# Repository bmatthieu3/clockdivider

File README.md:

# Clock Divider module - Demo [here](https://youtu.be/5VTIWuq25X8)

A clock divider is usually a very important module in a modular synth as it can allow you to give the tempo to many other modules of your synth.
Here are some useful examples showing why it can be good to have a clock divider:

* Provide a /2, /4, /8 clock allowing to trigger drum sounds every 2, 4 or 8 cycles or any other events.
* Do Polyrhythm thanks to impair dividing ratio: /3, /5, /7!
* Mess a little bit the rythm thanks to a CV rotating input. This input accepts 0->5 volts. 0 volt means the outputs are not rotated, the first output gives a clock having the same frequency, the second one having half the input clock frequency, the third having one-third of the frequency... 5/8 volt will rotate the outputs of one output: the first output will be one-eight of the input clock frequency, the second output will give the same frequency, the third output will give the half of the input frequency... the eight's output will give one-seven of the first frequency.

# What does this repo contain

* The code for the Atmega328p in clock_divider.ino
* The electrical scheme for the module openable with kicad

* The pcd footprint for kicad (There is a 1k resistor missing between VCC (5V) and pin 6 of the uC. This is for the dividing potar to work, the main features (division of the clock signal frequency by 1 -> 8, the reset of the outputs and the rotating CV) will work without correcting this).
* The .svg showing the interface plate of the module. This is a very simple one that I did very fast, it is not very good at all. I recommand you to do your own if you want to build the module for your own synth. It will be of your taste and what is from you is always the best as a DIYer.
* The .stl file of the interface plate (made with blender)
* The .stl transformed in .gcode to print it.

# What does it look like

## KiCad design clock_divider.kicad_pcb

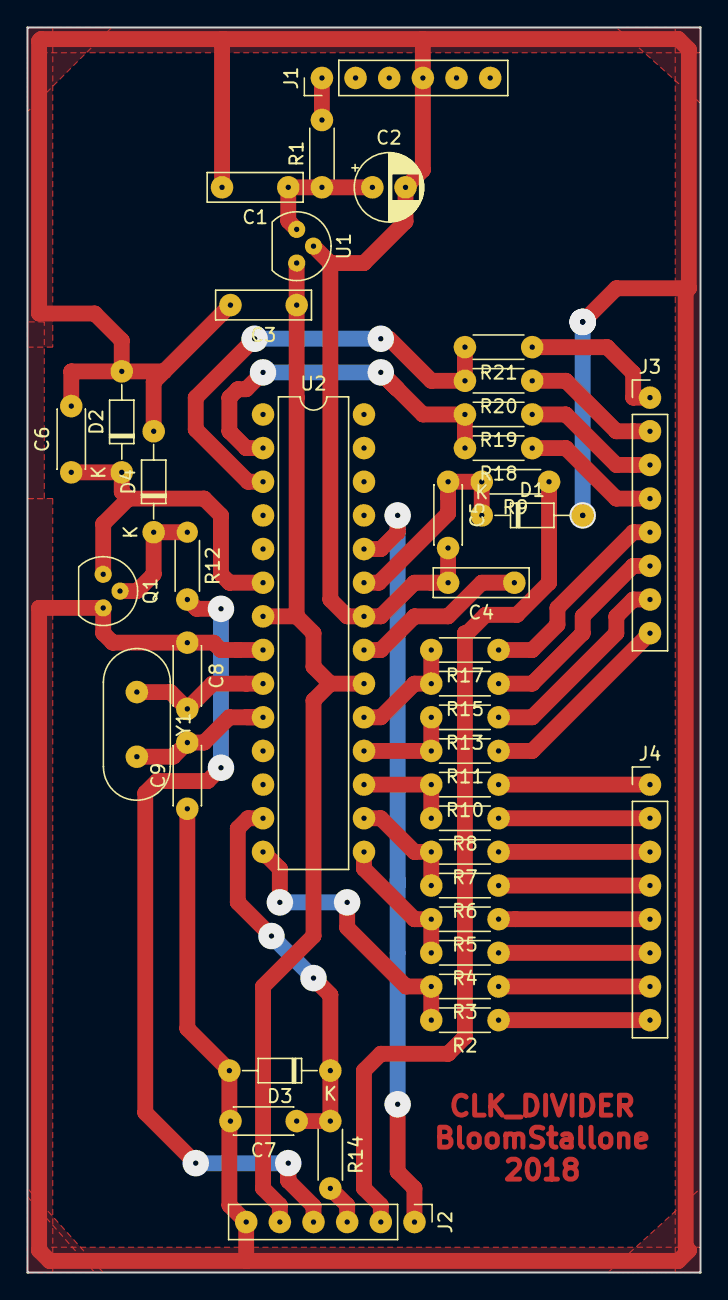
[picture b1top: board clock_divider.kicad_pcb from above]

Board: 2 copper layers, 50.8 x 94.0 mm, 41 parts (0 on the bottom side), 39 nets.

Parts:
C1, C3, C4: 100nF; C_Rect_L7.0mm_W2.0mm_P5.00mm
C2: 22uF; CP_Radial_D5.0mm_P2.50mm
C5, C6, C7: 220pF; C_Disc_D4.3mm_W1.9mm_P5.00mm
C8, C9: 22pF; C_Disc_D4.3mm_W1.9mm_P5.00mm
D1, D2, D3: D_Zener; D_DO-34_SOD68_P7.62mm_Horizontal
D4: D; D_DO-34_SOD68_P7.62mm_Horizontal
J1, J2: Conn_01x06_Male; PinHeader_1x06_P2.54mm_Vertical
J3, J4: Conn_01x08_Male; PinHeader_1x08_P2.54mm_Vertical
Q1: BC547; TO-92
R1: 10; R_Axial_DIN0204_L3.6mm_D1.6mm_P5.08mm_Horizontal
R2, R4, R6, R8, R11, R15, R18, R20: 330; R_Axial_DIN0204_L3.6mm_D1.6mm_P5.08mm_Horizontal
R3, R5, R7, R9, R10, R13, R14, R17, R19, R21: 1k; R_Axial_DIN0204_L3.6mm_D1.6mm_P5.08mm_Horizontal
R12: 470k; R_Axial_DIN0204_L3.6mm_D1.6mm_P5.08mm_Horizontal
U1: L7805; TO-92
U2: ATmega328-PU; DIP-28_W7.62mm
Y1: Crystal; Crystal_HC49-4H_Vertical

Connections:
/CLK1: J4.7, R3.1
/CLK2: J4.5, R5.1
/CLK3: J4.3, R7.1
/CLK4: J4.1, R10.1
/CLK5: J3.7, R13.1
/CLK6: J3.5, R17.1
/CLK7: J3.3, R19.1
/CLK8: J3.1, R21.1
/DIVIDING: J2.1, U2.24
/LED1: J4.8, R2.1
/LED2: J4.6, R4.1
/LED3: J4.4, R6.1
/LED4: J4.2, R8.1
/LED5: J3.8, R11.1
/LED6: J3.6, R15.1
/LED7: J3.4, R18.1
/LED8: J3.2, R20.1
/MASTER_CLK_IN: J2.3, R14.2
/PB0: R2.2, R3.2, U2.14
/PB1: R4.2, R5.2, U2.15
/PB2: R6.2, R7.2, U2.16
/PB3: R8.2, R10.2, U2.17
/PB4: R11.2, R13.2, U2.18
/PB5: R15.2, R17.2, U2.19
/PD0: R18.2, R19.2, U2.2
/PD1: R20.2, R21.2, U2.3
/RESET_IN: J2.4, R12.2
/ROTATE_IN: J2.2, R9.1
/VCC: C3.1, J2.5, U1.3, U2.7, U2.20
GND: C1.2, C2.2, C3.2, C4.2, C5.2, C6.2, C7.2, C8.1, C9.1, D1.2, D2.2, D3.2, D4.2, J1.4, J2.6, Q1.3, U1.2, U2.8, U2.22
unnamed: C1.1, C2.1, R1.1, U1.1
unnamed: C4.1, U2.21
unnamed: C5.1, D1.1, R9.2, U2.23
unnamed: C6.1, D2.1, Q1.1, U2.6
unnamed: C7.1, D3.1, R14.1, U2.13
unnamed: C8.2, U2.9, Y1.1
unnamed: C9.2, U2.10, Y1.2
unnamed: D4.1, Q1.2, R12.1
unnamed: J1.1, R1.2

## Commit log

2020-03-15 basic readme
2020-03-15 add images
2020-03-15 resize images
2020-03-15 scheme
2020-03-15 add license MIT
